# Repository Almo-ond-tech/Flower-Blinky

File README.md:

I made a 4 leafed clover shaped 555 Chaser led-board. It has 10 LEDs and was made using kicad

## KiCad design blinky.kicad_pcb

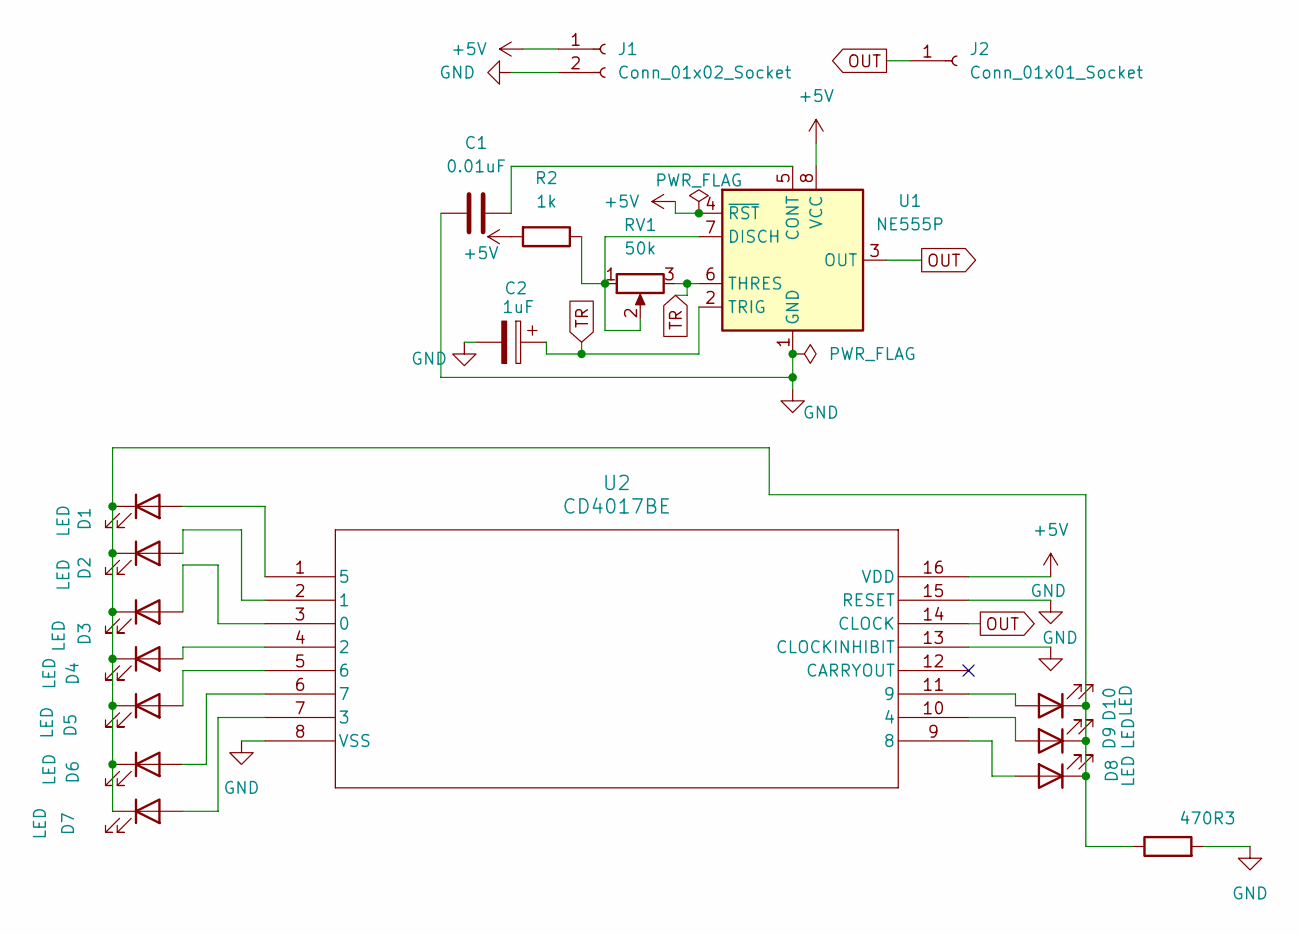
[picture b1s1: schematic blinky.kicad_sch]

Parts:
C1: 0.01uF; C_Disc_D9.0mm_W2.5mm_P5.00mm
C2: 1uF; CP_Radial_D5.0mm_P2.00mm
D1, D2, D3, D4, D5, D6, D7, D8, D9, D10: LED; LED_D3.0mm
J1: Conn_01x02_Socket; PinHeader_1x02_P2.54mm_Vertical
J2: Conn_01x01_Socket; PinHeader_1x01_P2.54mm_Vertical
R2: 1k; R_Axial_DIN0207_L6.3mm_D2.5mm_P7.62mm_Horizontal
R3: 470; R_Axial_DIN0207_L6.3mm_D2.5mm_P7.62mm_Horizontal
RV1: 50k; Potentiometer_Vishay_T93YA_Vertical
U1: NE555P; DIP-8_W7.62mm
U2: CD4017BE; N16

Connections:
+5V: J1.1, R2.2, U1.4 (~RST), U1.8 (VCC), U2.16 (VDD)
GND: C1.2, C2.2, J1.2, R3.2, U1.1 (GND), U2.8 (VSS), U2.13 (CLOCKINHIBIT), U2.15 (RESET)
unnamed: D1.2 (A), U2.1 (5)
unnamed: D1.1 (K), D2.1 (K), D3.1 (K), D4.1 (K), D5.1 (K), D6.1 (K), D7.1 (K), D8.1 (K), D9.1 (K), D10.1 (K), R3.1
unnamed: D2.2 (A), U2.2 (1)
unnamed: D3.2 (A), U2.3 (0)
unnamed: D4.2 (A), U2.4 (2)
unnamed: D5.2 (A), U2.5 (6)
unnamed: D6.2 (A), U2.6 (7)
unnamed: D7.2 (A), U2.7 (3)
unnamed: D8.2 (A), U2.9 (8)
unnamed: D9.2 (A), U2.10 (4)
unnamed: D10.2 (A), U2.11 (9)
unnamed: C1.1, U1.5 (CONT)
unnamed: R2.1, RV1.1, RV1.2, U1.7 (DISCH)
OUT: J2.1 (Pin_1_1), U1.3 (OUT), U2.14 (CLOCK)
TR: C2.1, RV1.3, U1.2 (TRIG), U1.6 (THRES)

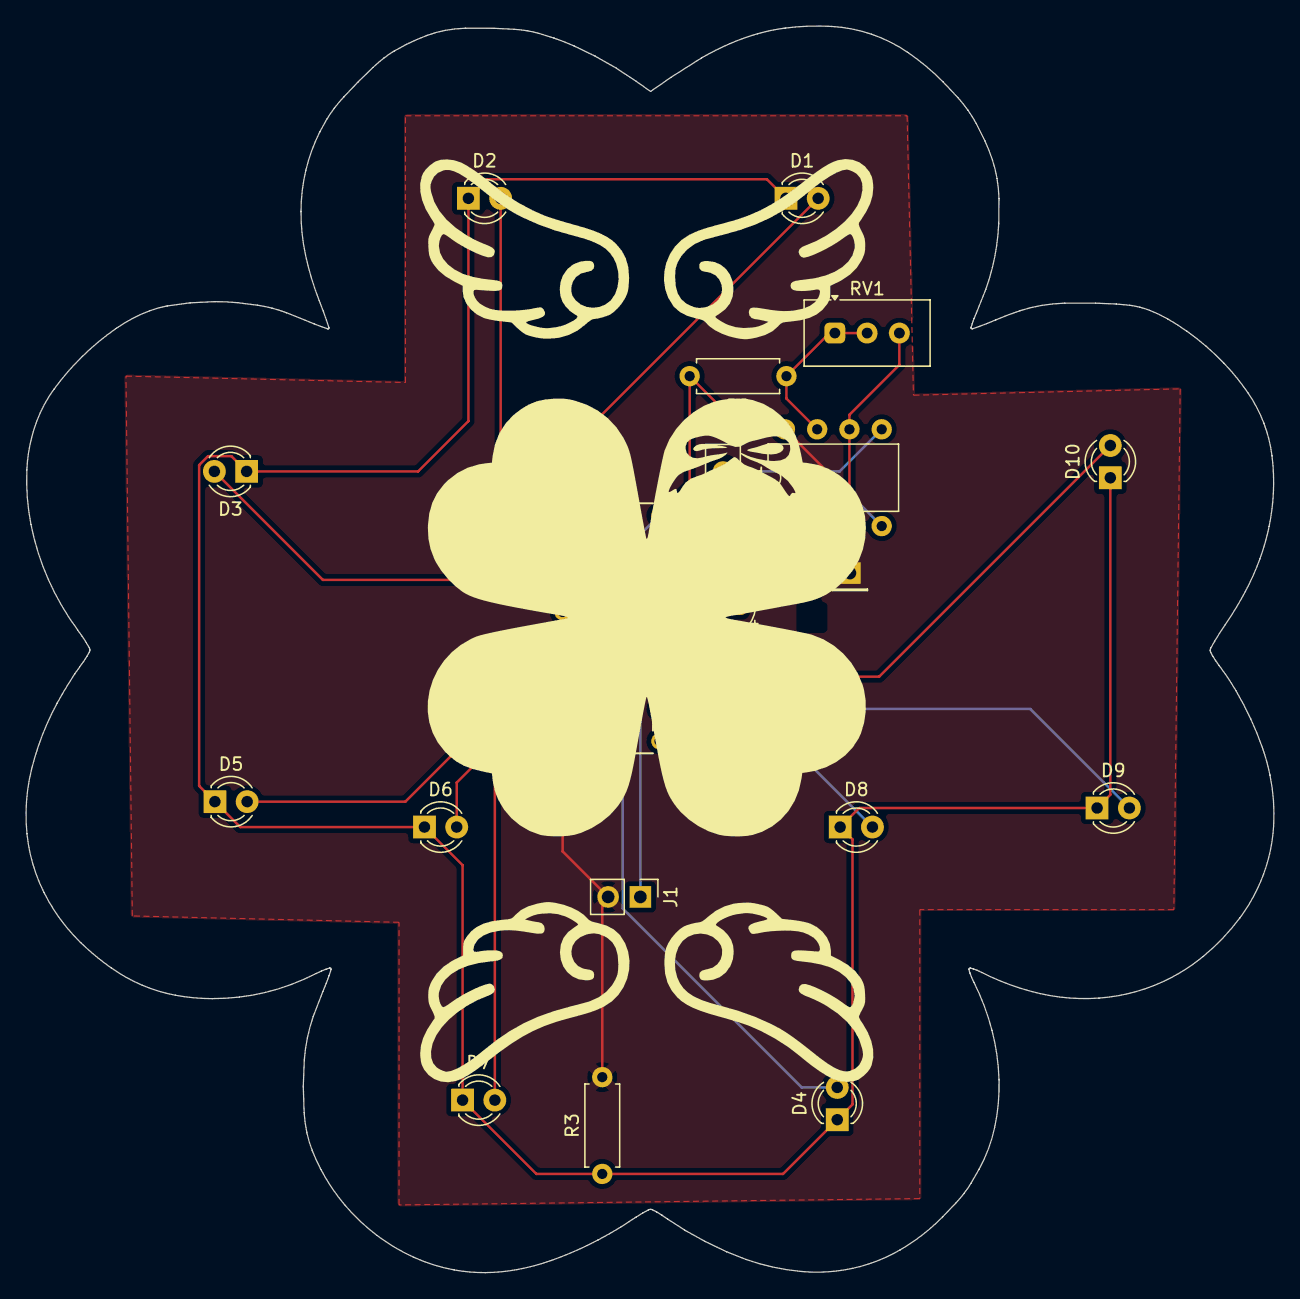
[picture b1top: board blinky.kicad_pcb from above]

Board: 2 copper layers, 98.3 x 98.1 mm, 19 parts (0 on the bottom side), 17 nets.

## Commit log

2026-04-14 README.md
2026-04-14 Rename front_screenshot.png to 3dfront_screenshot.png
2026-04-14 Rename front_screenshot.png to 3d-front_screenshot.png
